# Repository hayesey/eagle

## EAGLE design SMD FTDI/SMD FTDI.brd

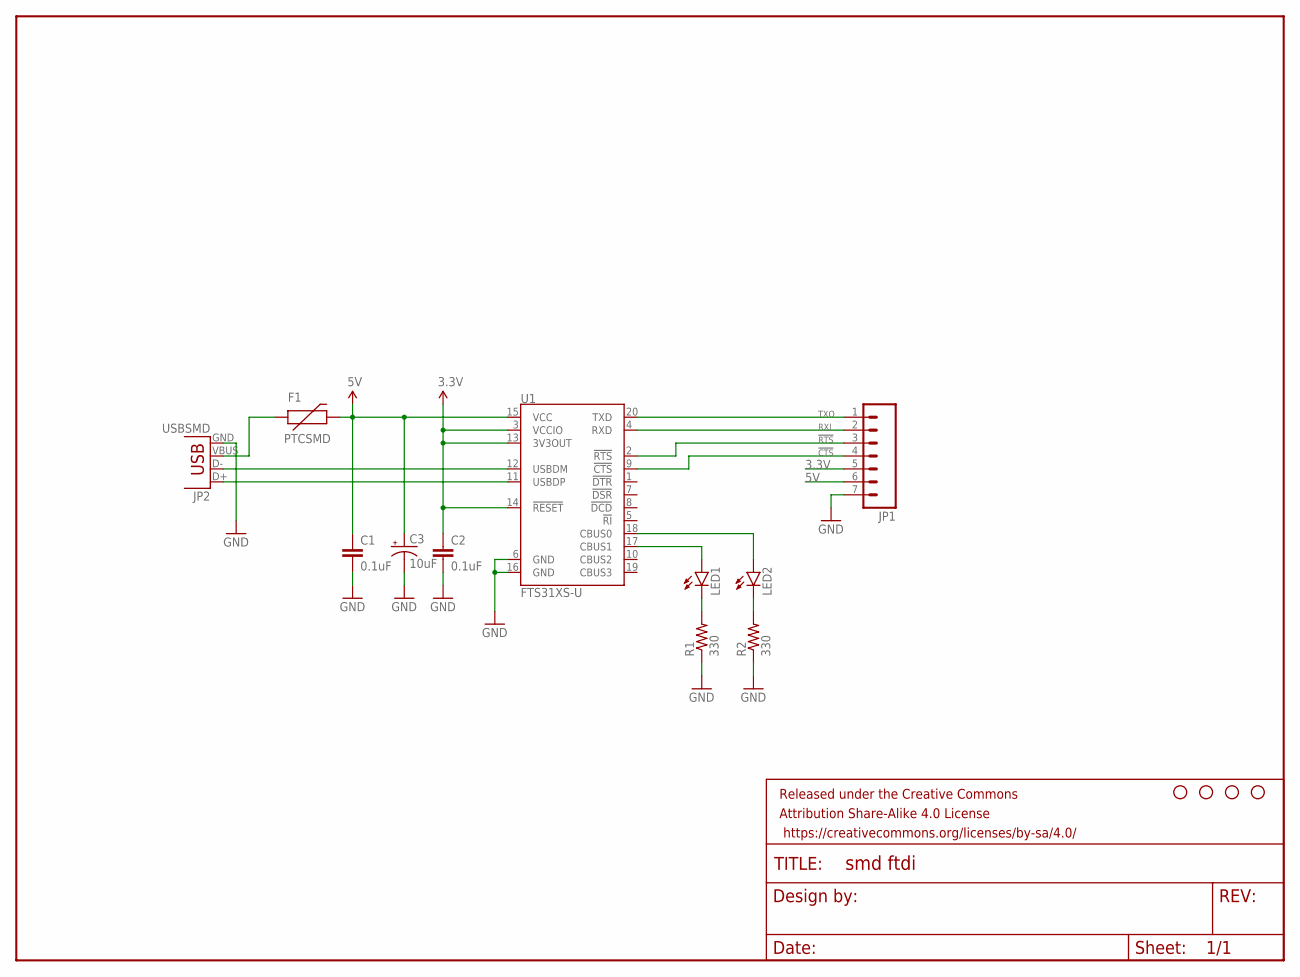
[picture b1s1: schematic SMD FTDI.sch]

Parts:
C1, C2: 0.1uF; 0603-CAP
C3: 10uF; EIA3216-KIT
F1: PTCSMD; PTC-1206
FRAME1: FRAME-LETTER; CREATIVE_COMMONS
JP1: M07; 1X07
JP2: USBSMD; USB-MINIB
LED1, LED2: LED0603; LED-0603
R1, R2: 330; 0603-RES
STANDOFF1, STANDOFF2, STANDOFF3, STANDOFF4: STAND-OFF
U1: FTS31XS-U; SSOP20_L

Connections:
3.3V: C2.1, JP1.5, U1.3 (VCCIO), U1.13 (3V3OUT), U1.14 (!RESET)
5V: C1.1, C3.A (+), F1.2, JP1.6, U1.15 (VCC)
!CTS: JP1.4, U1.9 (!CTS)
!RTS: JP1.3, U1.2 (!RTS)
GND: C1.2, C2.2, C3.C (-), JP1.7, JP2.GND, R1.1, R2.1, U1.6 (GND), U1.16 (GND)
unnamed: JP2.D-, U1.12 (USBDM)
unnamed: JP2.D+, U1.11 (USBDP)
unnamed: F1.1, JP2.VBUS
unnamed: LED2.A, U1.18 (CBUS0)
unnamed: LED1.A, U1.17 (CBUS1)
unnamed: LED1.C, R1.2
unnamed: LED2.C, R2.2
RXI: JP1.2, U1.4 (RXD)
TXO: JP1.1, U1.20 (TXD)

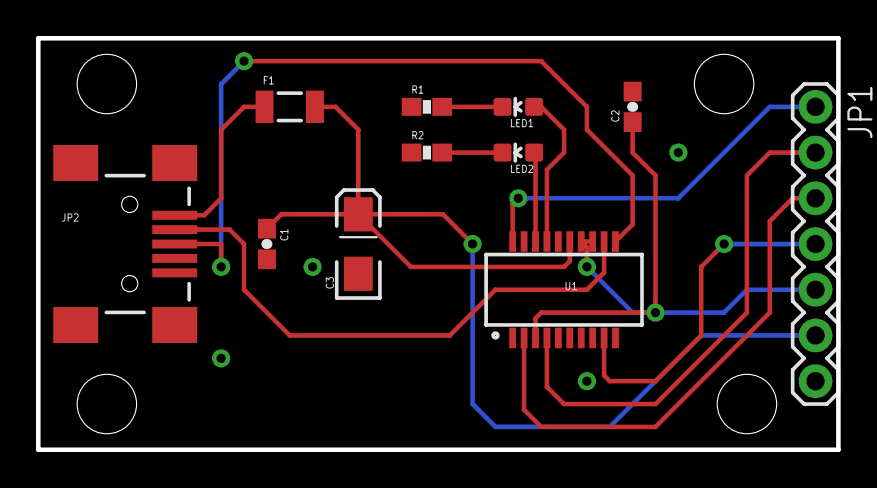
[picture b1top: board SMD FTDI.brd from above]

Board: 2 copper layers, 44.5 x 22.9 mm, 16 parts (0 on the bottom side), 14 nets.

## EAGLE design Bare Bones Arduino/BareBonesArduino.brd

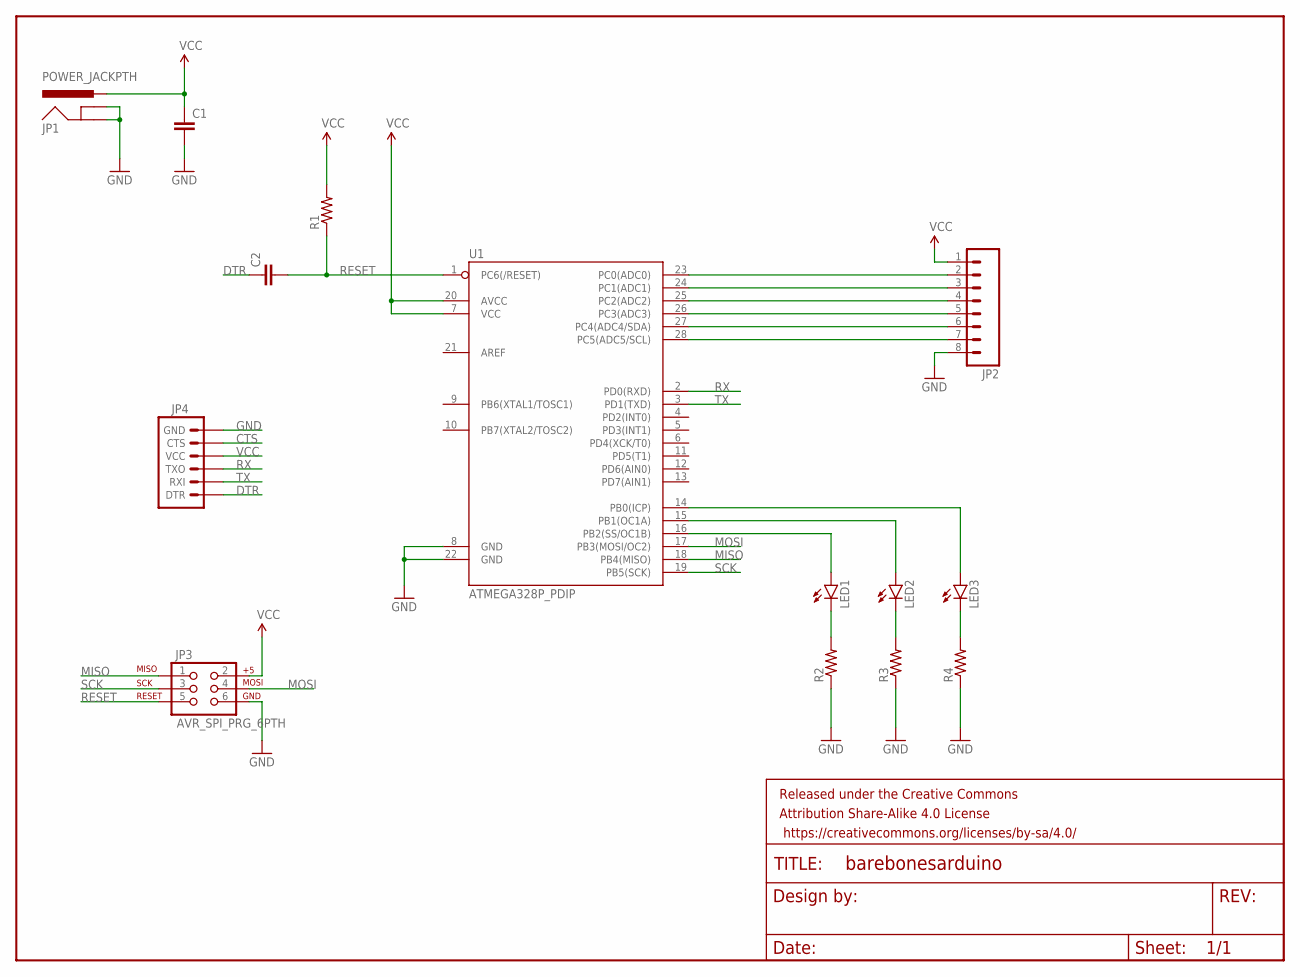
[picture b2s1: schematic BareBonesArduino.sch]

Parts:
C1, C2: CAPPTH; CAP-PTH-SMALL
FRAME1: FRAME-LETTER; CREATIVE_COMMONS
JP1: POWER_JACKPTH; POWER_JACK_PTH
JP2: M08; 1X08_ROUND
JP3: AVR_SPI_PRG_6PTH; 2X3
JP4: ARDUINO_SERIAL_PROGRAMPTH; 1X06
LED1, LED2, LED3: LED5MM
R1, R2, R3, R4: RESISTORPTH-1/4W; AXIAL-0.4
U1: ATMEGA328P_PDIP; DIL28-3

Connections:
CTS: JP4.5 (CTS)
DTR: C2.1, JP4.1 (DTR)
GND: C1.2, JP1.GND, JP1.GNDBREAK, JP2.8, JP3.6, JP4.6 (GND), R2.P$1 (1), R3.P$1 (1), R4.P$1 (1), U1.8 (GND), U1.22 (GND)
MISO: JP3.1, U1.18 (PB4(MISO))
MOSI: JP3.4, U1.17 (PB3(MOSI/OC2))
unnamed: JP2.2, U1.23 (PC0(ADC0))
unnamed: JP2.3, U1.24 (PC1(ADC1))
unnamed: JP2.4, U1.25 (PC2(ADC2))
unnamed: JP2.5, U1.26 (PC3(ADC3))
unnamed: JP2.6, U1.27 (PC4(ADC4/SDA))
unnamed: JP2.7, U1.28 (PC5(ADC5/SCL))
unnamed: LED1.A, U1.16 (PB2(SS/OC1B))
unnamed: LED2.A, U1.15 (PB1(OC1A))
unnamed: LED3.A, U1.14 (PB0(ICP))
unnamed: LED1.K (C), R2.P$2 (2)
unnamed: LED2.K (C), R3.P$2 (2)
unnamed: LED3.K (C), R4.P$2 (2)
RESET: C2.2, JP3.5, R1.P$1 (1), U1.1 (PC6(/RESET))
RX: JP4.3 (TXO), U1.2 (PD0(RXD))
SCK: JP3.3, U1.19 (PB5(SCK))
TX: JP4.2 (RXI), U1.3 (PD1(TXD))
VCC: C1.1, JP1.PWR, JP2.1, JP3.2, JP4.4 (VCC), R1.P$2 (2), U1.7 (VCC), U1.20 (AVCC)

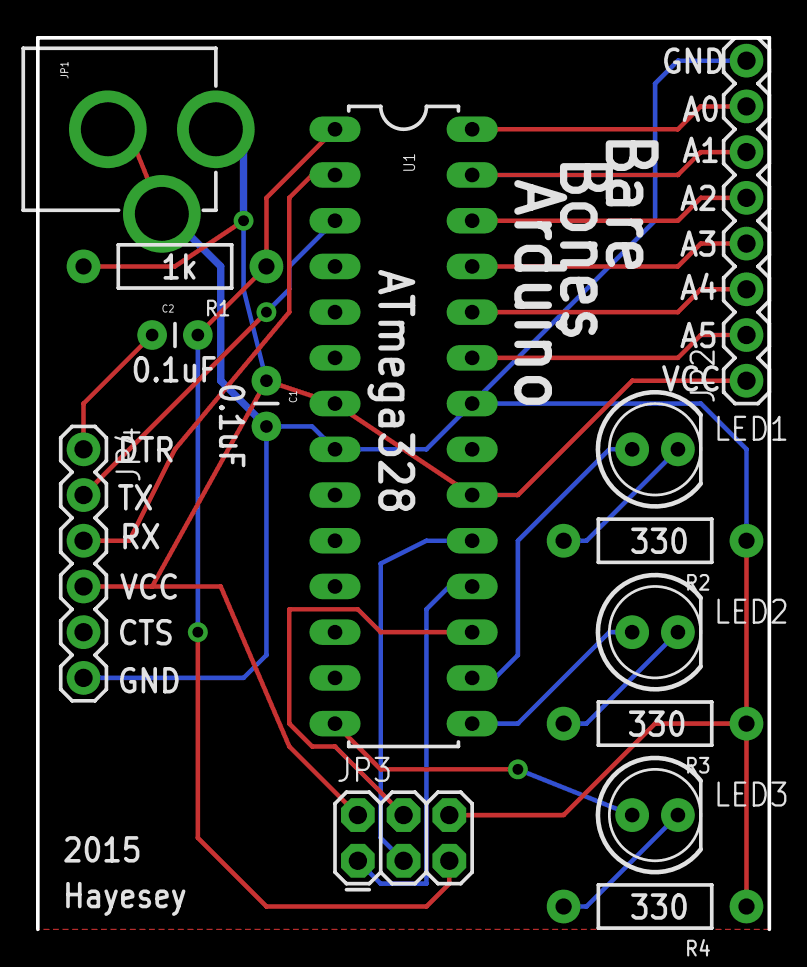
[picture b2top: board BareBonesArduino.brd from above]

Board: 2 copper layers, 40.6 x 49.5 mm, 15 parts (0 on the bottom side), 21 nets.

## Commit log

2015-12-17 initial commit of existing designs

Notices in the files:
parts and their libraries:
SparkFun-Capacitors: Licensing: Creative Commons ShareAlike 4.0 International - https://creativecommons.org/licenses/by-sa/4.0
SparkFun-Aesthetics: Released under the Creative Commons Attribution Share-Alike 4.0 License
SparkFun-Aesthetics: https://creativecommons.org/licenses/by-sa/4.0
